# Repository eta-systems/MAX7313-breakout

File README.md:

# MAX7313-breakout
Breakout Board for MAX7313 16 Channel Port Expander with 4 bit PWM

---

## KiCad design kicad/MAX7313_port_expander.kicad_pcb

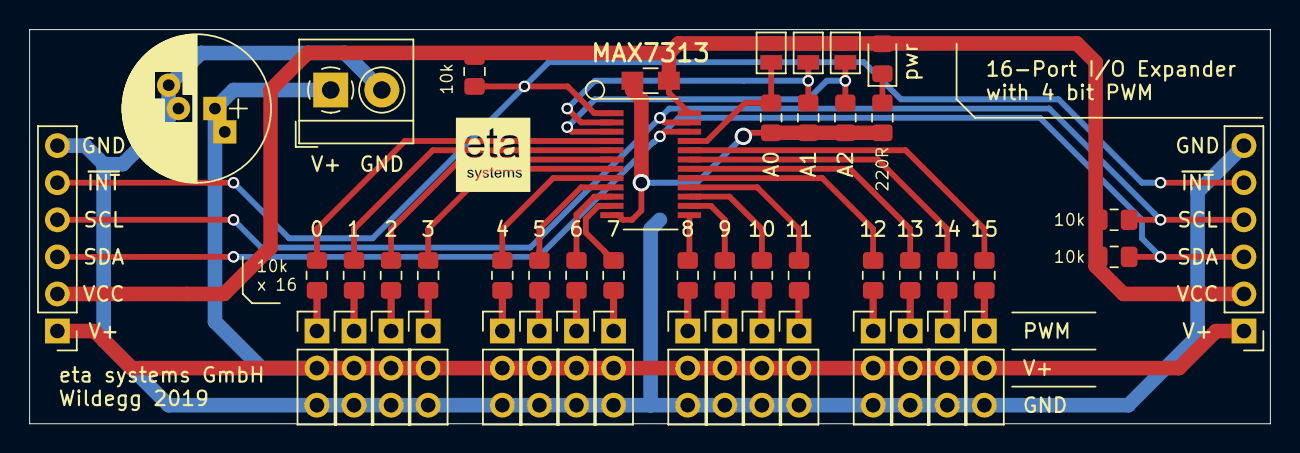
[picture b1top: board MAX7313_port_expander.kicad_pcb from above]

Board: 2 copper layers, 85.0 x 27.0 mm, 49 parts (0 on the bottom side), 42 nets.

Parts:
C101: C; CP_Radial_D10.0mm_P2.50mm_P5.00mm
C102: 10uF; C_0805_HandSoldering
D101: LED; LED_0805_2012Metric_Pad1.15x1.40mm_HandSolder
J101, J102, J103, J104, J105, J106, J107, J108, J109, J110, J111, J112, J113, J114, J115, J116: Conn_01x03; PinHeader_1x03_P2.54mm_Vertical
J117, J118: Conn_01x06; PinHeader_1x06_P2.54mm_Vertical
J119: Screw_Terminal_01x02; TerminalBlock_4Ucon_1x02_P3.50mm_Horizontal
JP101, JP102, JP103: Jumper_2_Open; SolderJumper-2_P1.3mm_Open_Pad1.0x1.5mm
R101, R102, R103, R104, R106, R107, R108, R109, R113, R114, R115, R116, R117, R118, R119, R120: 220; R_0805_2012Metric_Pad1.15x1.40mm_HandSolder
R105, R110, R111, R112, R122, R123: 10k; R_0805_2012Metric_Pad1.15x1.40mm_HandSolder
R121: 470; R_0805_2012Metric_Pad1.15x1.40mm_HandSolder
U101: MAX7313AEG+; QSOP-24_3.9x8.7mm_P0.635mm

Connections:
+3V3: C102.1, D101.2, J117.2, J118.2, JP101.1, JP102.1, JP103.1, R105.1, R122.1, R123.1, U101.24
+5V: C101.1, J101.2, J102.2, J103.2, J104.2, J105.2, J106.2, J107.2, J108.2, J109.2, J110.2, J111.2, J112.2, J113.2, J114.2, J115.2, J116.2, J117.1, J118.1, J119.1
/PWM0: R101.2, U101.4
/PWM1: R103.2, U101.5
/PWM2: R106.2, U101.6
/PWM3: R108.2, U101.7
/PWM4: R113.2, U101.8
/PWM5: R115.2, U101.9
/PWM6: R117.2, U101.10
/PWM7: R119.2, U101.11
/PWM8: R102.2, U101.13
/PWM9: R104.2, U101.14
/PWM10: R107.2, U101.15
/PWM11: R109.2, U101.16
/PWM12: R114.2, U101.17
/PWM13: R116.2, U101.18
/PWM14: R118.2, U101.19
/PWM15: R120.2, U101.20
/SCL: J117.4, J118.4, R122.2, U101.23
/SDA: J117.3, J118.3, R123.2, U101.22
GND: C101.2, C102.2, J101.3, J102.3, J103.3, J104.3, J105.3, J106.3, J107.3, J108.3, J109.3, J110.3, J111.3, J112.3, J113.3, J114.3, J115.3, J116.3, J117.6, J118.6, J119.2, R110.2, R111.2, R112.2, R121.1, U101.12
unnamed: D101.1, R121.2
unnamed: J101.1, R101.1
unnamed: J102.1, R102.1
unnamed: J103.1, R103.1
unnamed: J104.1, R104.1
unnamed: J105.1, R106.1
unnamed: J106.1, R107.1
unnamed: J107.1, R108.1
unnamed: J108.1, R109.1
unnamed: J109.1, R113.1
unnamed: J110.1, R114.1
unnamed: J111.1, R115.1
unnamed: J112.1, R116.1
unnamed: J113.1, R117.1
unnamed: J114.1, R118.1
unnamed: J115.1, R119.1
unnamed: J116.1, R120.1
unnamed: JP101.2, R110.1, U101.21
unnamed: JP102.2, R111.1, U101.2
unnamed: JP103.2, R112.1, U101.3
~INT~: J117.5, J118.5, R105.2, U101.1

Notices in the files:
README.md:
https://forthebadge.com/images/badges/cc-by.svg
